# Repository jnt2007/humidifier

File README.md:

# humidifier
ESP8266 controller for Polaris PUH 5304 air humidifier

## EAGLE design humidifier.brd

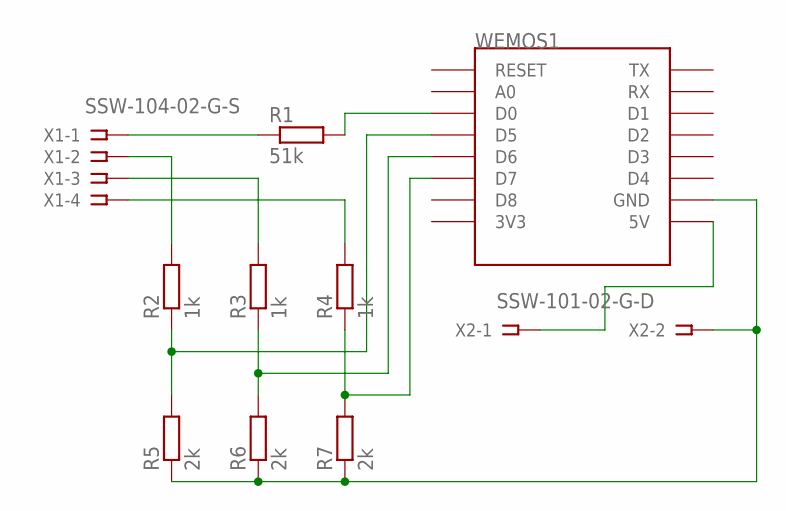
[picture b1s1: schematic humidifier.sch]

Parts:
R1: 51k; R1206
R2, R3, R4: 1k; R1206
R5, R6, R7: 2k; R1206
WEMOS1: WEMOS-D1-MINI
X1: SSW-104-02-G-S
X2: SSW-101-02-G-D

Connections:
unnamed: R5.1, R6.1, R7.1, WEMOS1.GND, X2.2
unnamed: WEMOS1.5V, X2.1
unnamed: R2.2, X1.2
unnamed: R3.2, X1.3
unnamed: R4.2, X1.4
unnamed: R2.1, R5.2, WEMOS1.D5
unnamed: R3.1, R6.2, WEMOS1.D6
unnamed: R4.1, R7.2, WEMOS1.D7
unnamed: R1.1, X1.1
unnamed: R1.2, WEMOS1.D0

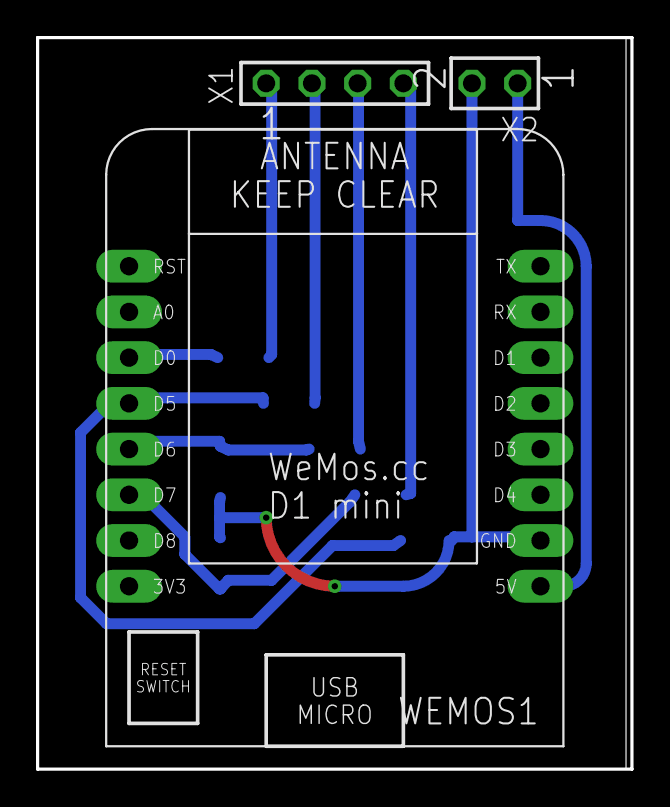
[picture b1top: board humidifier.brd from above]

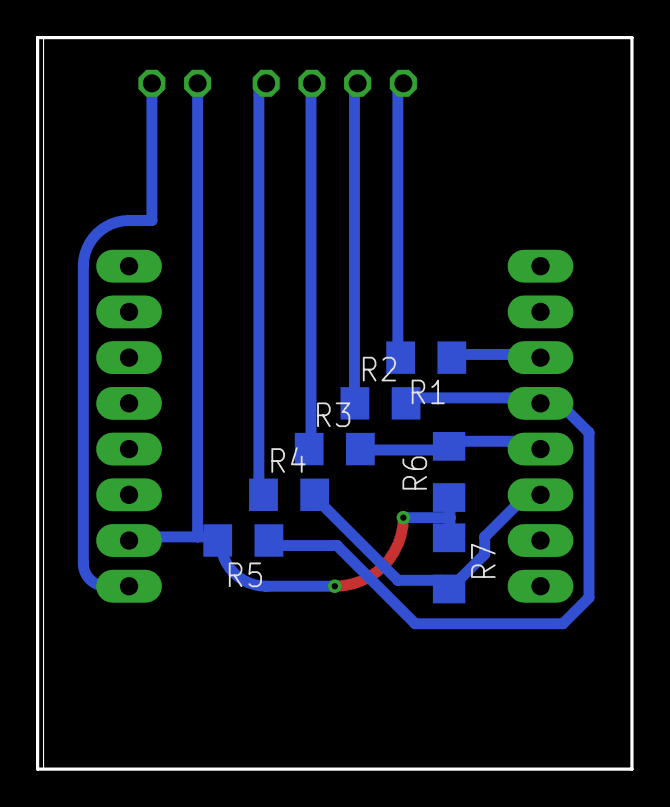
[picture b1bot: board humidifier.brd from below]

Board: 2 copper layers, 33.0 x 40.6 mm, 10 parts (7 on the bottom side), 10 nets.

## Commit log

2019-01-03 First upload
2019-02-10 Updated read and reporting logic
2019-04-02 Added OTA upgrade functionality
2021-05-25 Optimization
